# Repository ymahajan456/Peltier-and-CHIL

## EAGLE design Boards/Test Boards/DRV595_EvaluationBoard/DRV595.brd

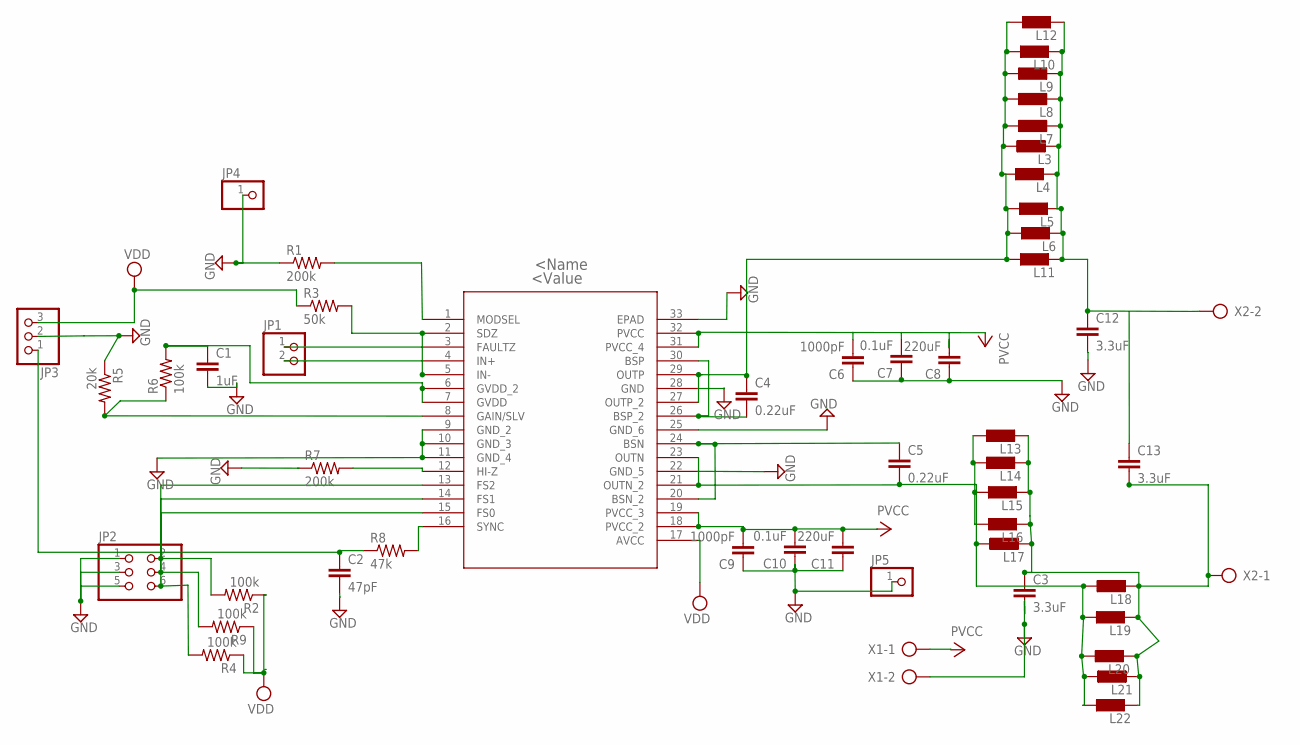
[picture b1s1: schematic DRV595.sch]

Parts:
C1: 1uF; C2.5-3
C2: 47pF; C2.5-3
C3, C12, C13: 3.3uF; C2.5-3
C4, C5: 0.22uF; C2.5-3
C6, C9: 1000pF; C2.5-3
C7, C10: 0.1uF; C2.5-3
C8, C11: 220uF; C2.5-3
JP1: PINHD-1X2; 1X02
JP2: PINHD-2X3; 2X03
JP3: PINHD-1X3; 1X03
JP4, JP5: PINHD-1X1; 1X01
L3, L4, L5, L6, L7, L8, L9, L10, L11, L12, L13, L14, L15, L16, L17, L18, L19, L20, L21, L22: L0207/10; 0207/10
R1, R7: 200k; 0207/10
R2, R4, R6, R9: 100k; 0207/10
R3: 50k; 0207/10
R5: 20k; 0207/10
R8: 47k; 0207/10
U1: DRV595DAPRDAP32_4P11X4P36-L; DAP32_4P11X4P36-L
X1: AK300/2
X2: AK500/2-H

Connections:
GND: C1.2, C2.2, C3.2, C6.1, C7.1, C8.1, C9.1, C10.1, C11.1, C12.2, JP2.1, JP2.3, JP2.5, JP3.2, JP4.1, JP5.1, R1.1, R5.1, R7.1, U1.9 (GND_2), U1.10 (GND_3), U1.11 (GND_4), U1.22 (GND_5), U1.25 (GND_6), U1.28 (GND), U1.33 (EPAD), X1.2
unnamed: R1.2, U1.1 (MODSEL)
unnamed: JP1.1, U1.4 (IN+)
unnamed: R3.2, U1.2 (SDZ), U1.3 (FAULTZ)
unnamed: R5.2, R6.1, U1.8 (GAIN/SLV)
unnamed: C1.1, R6.2, U1.6 (GVDD_2), U1.7 (GVDD)
unnamed: R7.2, U1.12 (HI-Z)
unnamed: R8.2, U1.16 (SYNC)
unnamed: C2.1, JP3.1, R8.1
unnamed: JP2.2, R2.2, U1.13 (FS2)
unnamed: C5.1, U1.20 (BSN_2), U1.24 (BSN)
unnamed: C4.2, U1.26 (BSP_2), U1.30 (BSP)
unnamed: JP2.4, R9.2, U1.14 (FS1)
unnamed: JP1.2, U1.5 (IN-)
unnamed: JP2.6, R4.2, U1.15 (FS0)
unnamed: C3.1, C13.2, L13.2, L14.2, L15.2, L16.2, L17.2, L18.2, L19.2, L20.2, L21.2, L22.2, X2.1
unnamed: C12.1, C13.1, L3.2, L4.2, L5.2, L6.2, L7.2, L8.2, L9.2, L10.2, L11.2, L12.2, X2.2
unnamed: C5.2, L13.1, L14.1, L15.1, L16.1, L17.1, L18.1, L19.1, L20.1, L21.1, L22.1, U1.21 (OUTN_2), U1.23 (OUTN)
unnamed: C4.1, L3.1, L4.1, L5.1, L6.1, L7.1, L8.1, L9.1, L10.1, L11.1, L12.1, U1.27 (OUTP_2), U1.29 (OUTP)
VCC: C6.2, C7.2, C8.2, C9.2, C10.2, C11.2, U1.18 (PVCC_2), U1.19 (PVCC_3), U1.31 (PVCC_4), U1.32 (PVCC), X1.1
VDD: JP3.3, R2.1, R3.1, R4.1, R9.1, U1.17 (AVCC)

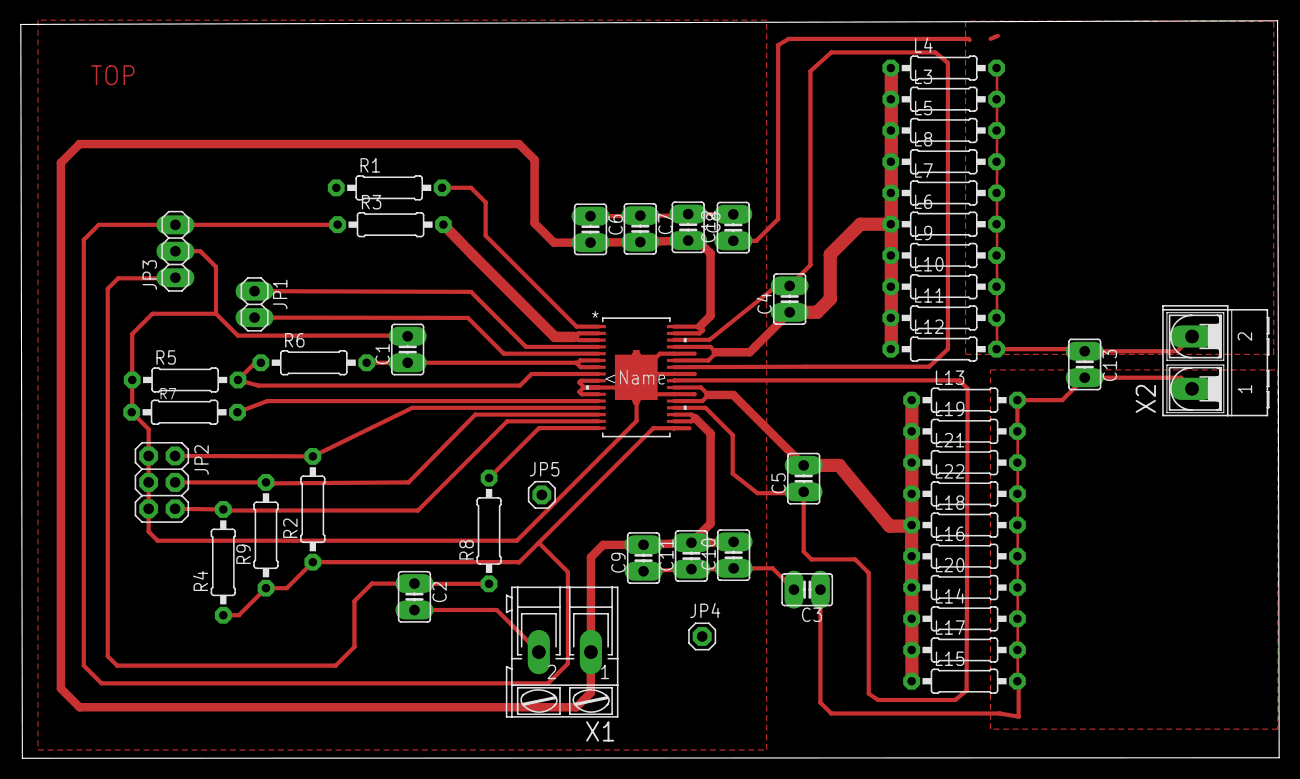
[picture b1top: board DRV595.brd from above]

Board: 2 copper layers, 120.9 x 70.8 mm, 50 parts (0 on the bottom side), 21 nets.

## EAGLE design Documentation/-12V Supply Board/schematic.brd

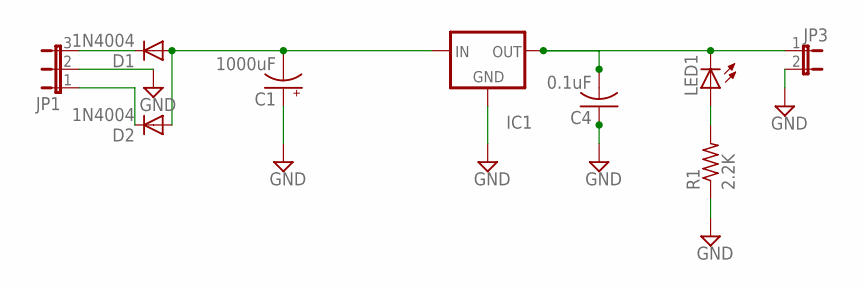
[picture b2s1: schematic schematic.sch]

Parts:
C1: 1000uF; E5-10,5
C4: 0.1uF; C050-025X075
D1, D2: 1N4004; DO41-10
IC1: 79XXS
JP1: JP2E; JP2
JP3: JP1E; JP1
LED1: LED5MM
R1: 2.2K; 0309/12

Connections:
GND: C1.+, C4.1, IC1.GND, JP1.2, JP3.2, R1.1
unnamed: D1.C, JP1.3
unnamed: D2.C, JP1.1
unnamed: C1.-, D1.A, D2.A, IC1.IN
unnamed: LED1.A, R1.2
unnamed: C4.2, IC1.OUT, JP3.1, LED1.K (C)

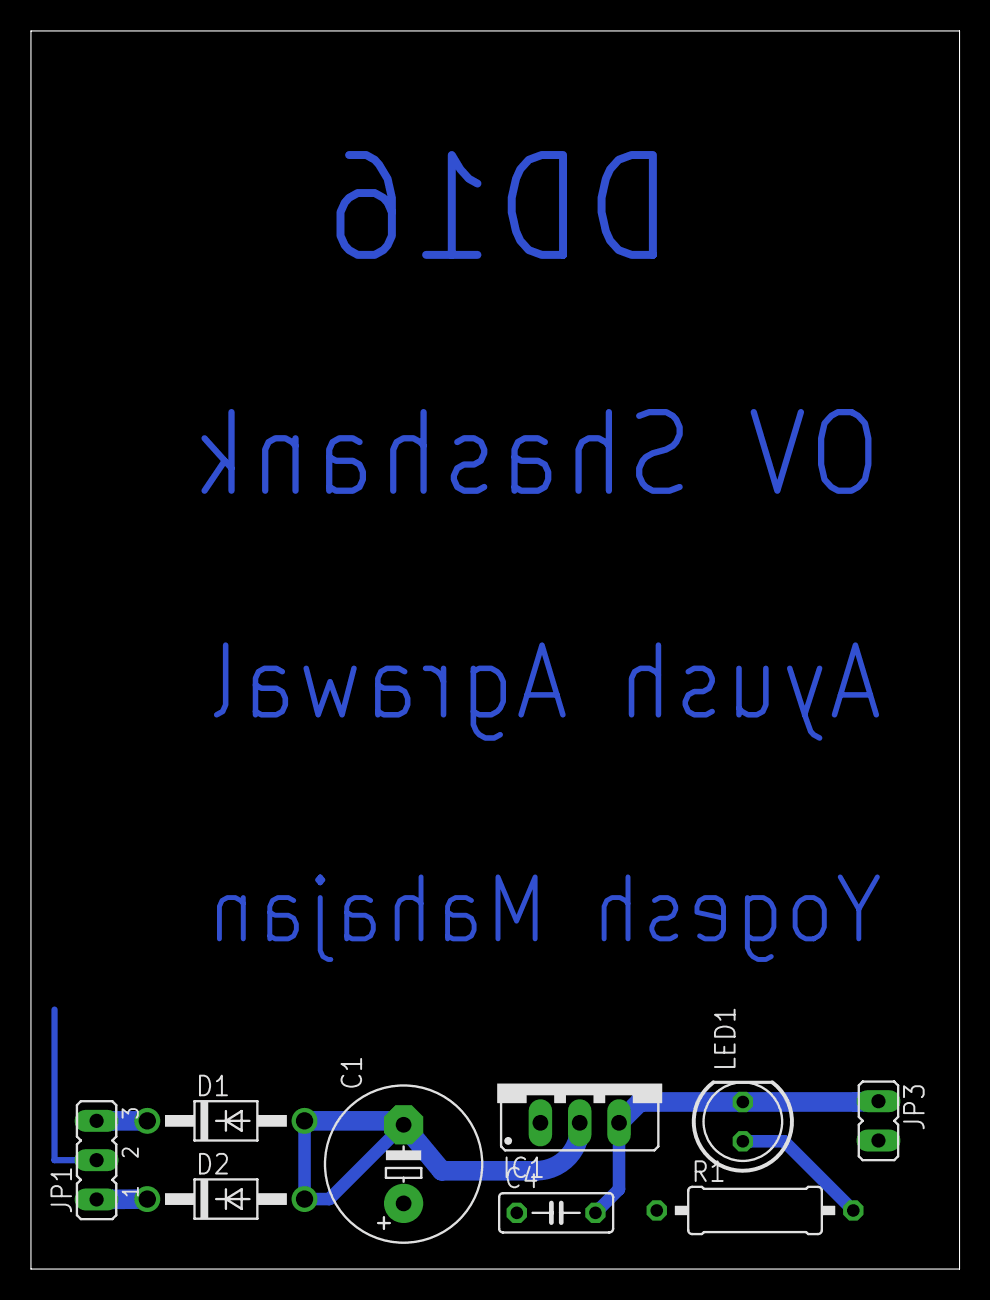
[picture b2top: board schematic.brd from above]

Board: 2 copper layers, 60.0 x 80.0 mm, 9 parts (0 on the bottom side), 6 nets.

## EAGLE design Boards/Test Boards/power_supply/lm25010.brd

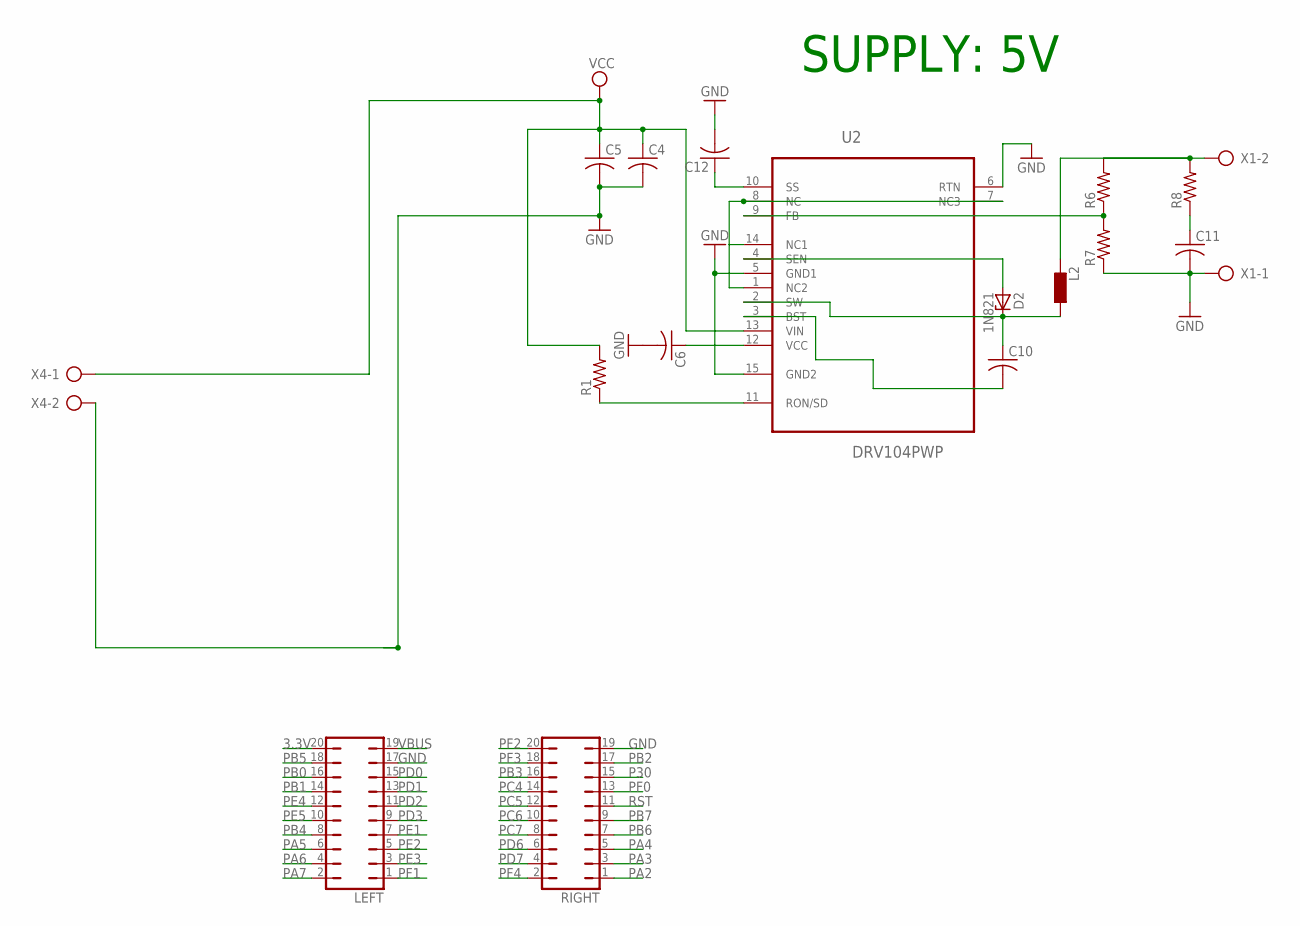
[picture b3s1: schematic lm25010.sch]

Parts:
C4, C5, C6, C10, C11, C12: C-US025-024X044; C025-024X044
D2: 1N821; DO35Z10
L2: L0207/10; 0207/10
LEFT: JP10Q
R1, R6, R7, R8: R-US_0207/10; 0207/10
RIGHT: JP10Q
U2: DRV104PWP; SOP65P640X120-15N
X1, X4: AK300/2

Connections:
3.3V: LEFT.20
GND: C4.2, C5.2, C6.2, C11.2, C12.2, LEFT.17, R7.1, RIGHT.19, U2.5 (GND1), U2.6 (RTN), U2.15 (GND2), X1.1, X4.2
unnamed: U2.1 (NC2), U2.7 (NC3), U2.8 (NC), U2.14 (NC1)
unnamed: R1.1, U2.11 (RON/SD)
unnamed: C12.1, U2.10 (SS)
unnamed: C6.1, U2.12 (VCC)
unnamed: C11.1, R8.1
unnamed: L2.2, R6.2, R8.2, X1.2
unnamed: R6.1, R7.2, U2.9 (FB)
unnamed: D2.A, U2.4 (SEN)
unnamed: C10.1, D2.C, L2.1, U2.2 (SW)
unnamed: C10.2, U2.3 (BST)
P30: RIGHT.15
PA2: RIGHT.1
PA3: RIGHT.3
PA4: RIGHT.5
PA5: LEFT.6
PA6: LEFT.4
PA7: LEFT.2
PB0: LEFT.16
PB1: LEFT.14
PB2: RIGHT.17
PB3: RIGHT.16
PB4: LEFT.8
PB5: LEFT.18
PB6: RIGHT.7
PB7: RIGHT.9
PC4: RIGHT.14
PC5: RIGHT.12
PC6: RIGHT.10
PC7: RIGHT.8
PD0: LEFT.15
PD1: LEFT.13
PD2: LEFT.11
PD3: LEFT.9
PD6: RIGHT.6
PD7: RIGHT.4
PE1: LEFT.7
PE2: LEFT.5
PE3: LEFT.3
PE4: LEFT.12
PE5: LEFT.10
PF0: RIGHT.13
PF1: LEFT.1
PF2: RIGHT.20
PF3: RIGHT.18
PF4: RIGHT.2
RST: RIGHT.11
VBUS: LEFT.19
VCC: C4.1, C5.1, R1.2, U2.13 (VIN), X4.1

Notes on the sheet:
SUPPLY: 5V

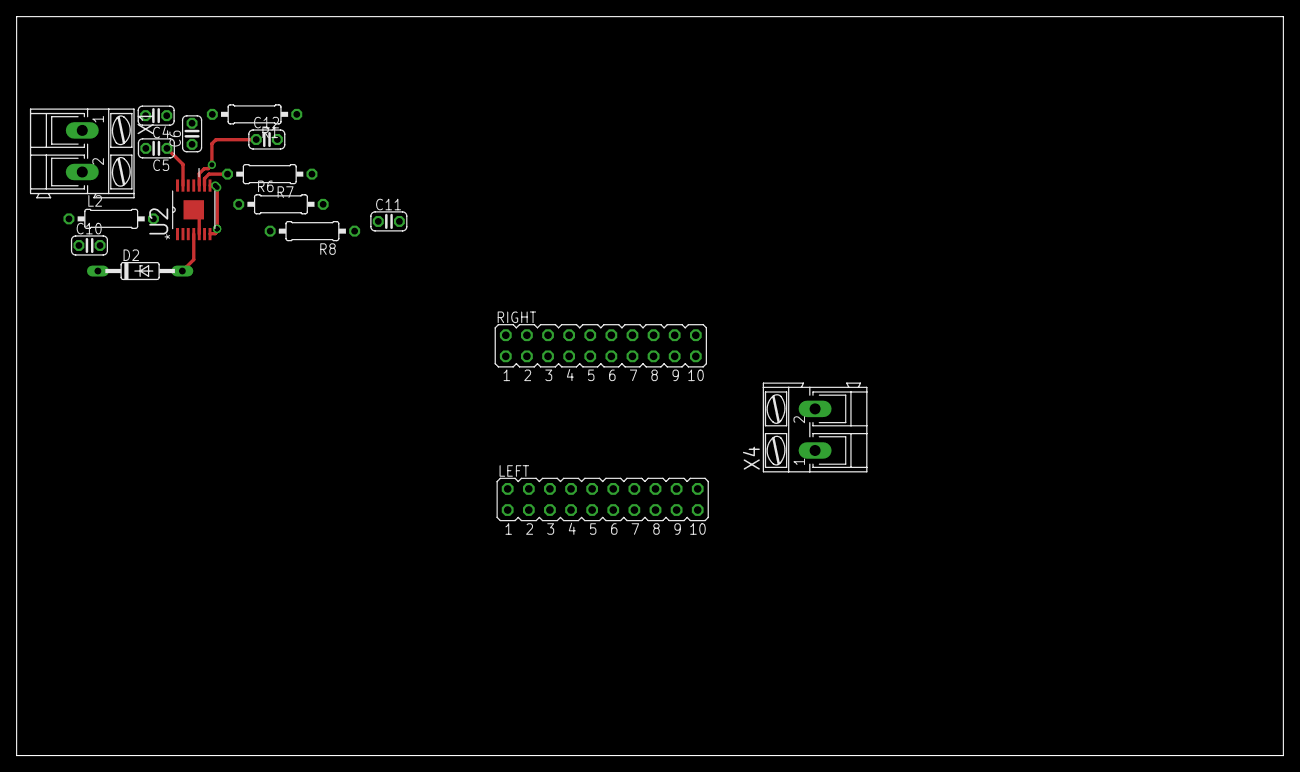
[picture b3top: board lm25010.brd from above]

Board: 2 copper layers, 152.4 x 88.9 mm, 17 parts (0 on the bottom side), 12 nets.

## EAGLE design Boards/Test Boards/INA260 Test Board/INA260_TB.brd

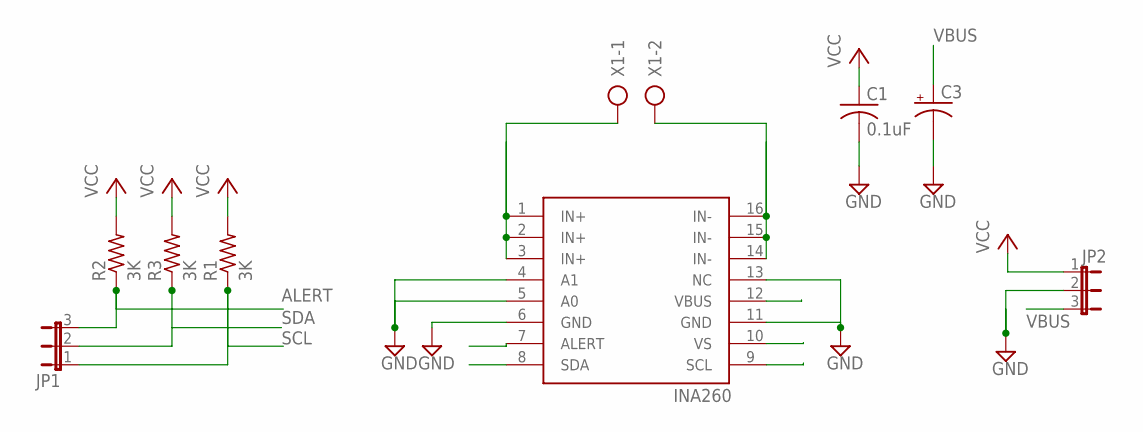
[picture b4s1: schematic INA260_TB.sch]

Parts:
C1: 0.1uF; C050-025X075
C3: CPOL-USE5-10.5; E5-10,5
JP1, JP2: JP2E; JP2
R1, R2, R3: 3K; 0207/10
U$1: INA260; TSSOP16
X1: AK300/2

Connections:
ALERT: JP1.3, R2.1, U$1.7 (ALERT)
GND: C1.2, C3.-, JP2.2, U$1.4 (A1), U$1.5 (A0), U$1.6 (GND), U$1.11 (GND), U$1.13 (NC)
unnamed: U$1.1 (IN+), U$1.2 (IN+), U$1.3 (IN+), X1.1
unnamed: U$1.14 (IN-), U$1.15 (IN-), U$1.16 (IN-), X1.2
SCL: JP1.1, R1.1, U$1.9 (SCL)
SDA: JP1.2, R3.1, U$1.8 (SDA)
VBUS: C3.+, JP2.3, U$1.12 (VBUS)
VCC: C1.1, JP2.1, R1.2, R2.2, R3.2, U$1.10 (VS)

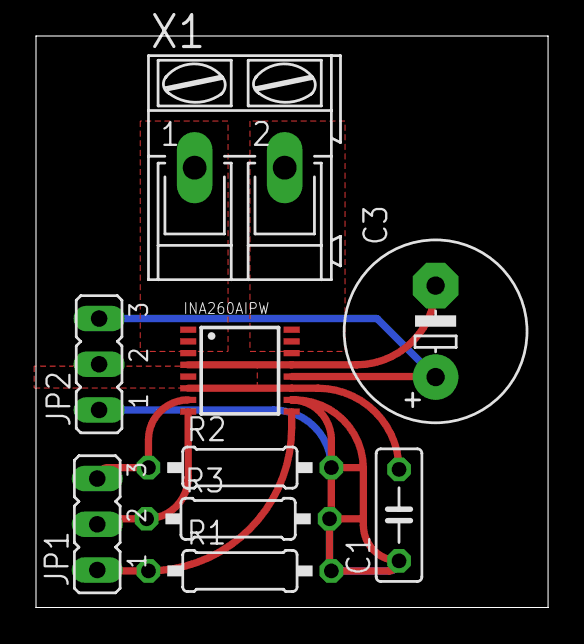
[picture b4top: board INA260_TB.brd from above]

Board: 2 copper layers, 28.4 x 31.8 mm, 9 parts (0 on the bottom side), 8 nets.

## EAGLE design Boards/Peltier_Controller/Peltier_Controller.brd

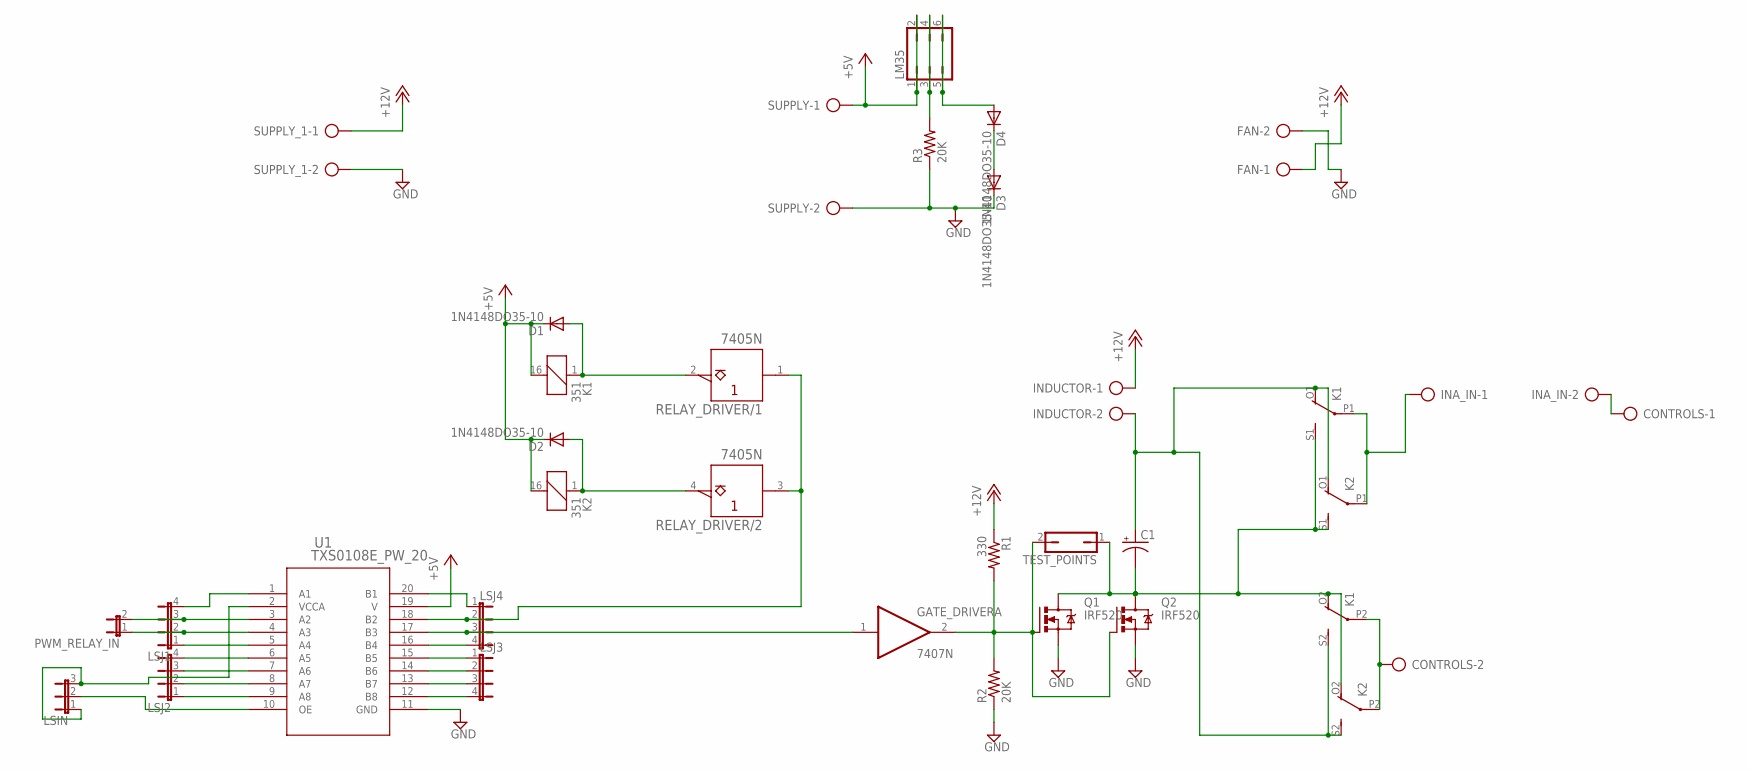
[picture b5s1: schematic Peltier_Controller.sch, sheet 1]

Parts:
C1: CPOL-USTT6D6; TT5D6
CONTROLS: AK500/2-H
D1, D2, D3, D4: 1N4148DO35-10; DO35-10
FAN: AK500/2-H
GATE_DRIVER: 7407N; DIL14
INA_IN: AK500/2-H
INDUCTOR: AK500/2-H
K1, K2: 351
LM35: JP3Q
LSIN: JP2E; JP2
LSJ1, LSJ2, LSJ3, LSJ4: JP4E; JP4
PWM_RELAY_IN: JP1E; JP1
Q1, Q2: IRF520; TO220BV
R1: 330; 0207/12
R2, R3: 20K; 0207/12
RELAY_DRIVER: 7405N; DIL14
SUPPLY: AK500/2-H
SUPPLY_1: AK500/2-H
TEST_POINTS: JP1Q; JP1
U1: TXS0108E_PW_20; PW20

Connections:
+5V: D1.C, D2.C, GATE_DRIVER.14 (VCC), K1.16 (2), K2.16 (2), LM35.1, LM35.2, RELAY_DRIVER.14 (+UB), SUPPLY.1, U1.19 (V); also elsewhere on the board
+12V: FAN.1, INDUCTOR.1, R1.1, SUPPLY_1.1
GND: D3.C, FAN.2, GATE_DRIVER.7 (GND), Q1.S, Q2.S, R2.1, R3.1, RELAY_DRIVER.7 (-UB), SUPPLY.2, SUPPLY_1.2, U1.11 (GND); also elsewhere on the board
IN+: CONTROLS.1, INA_IN.2; also elsewhere on the board
IN-: INA_IN.1, K1.P1, K2.P1; also elsewhere on the board
unnamed: LSJ1.3, PWM_RELAY_IN.2, U1.3 (A2)
unnamed: D2.A, K2.1, RELAY_DRIVER.4 (Y)
unnamed: LM35.3, LM35.4, R3.2
unnamed: D1.A, K1.1, RELAY_DRIVER.2 (Y)
unnamed: GATE_DRIVER.2 (O), Q1.G, Q2.G, R1.2, R2.2, TEST_POINTS.2
unnamed: D4.A, LM35.5, LM35.6
unnamed: D3.A, D4.C
unnamed: LSJ1.4, U1.1 (A1)
unnamed: LSJ4.1, U1.20 (B1)
unnamed: CONTROLS.2, K1.P2, K2.P2
unnamed: C1.-, K1.O2 (O), K1.S1 (S), K2.O2 (O), K2.S1 (S), Q1.D, Q2.D, TEST_POINTS.1
unnamed: LSJ1.2, PWM_RELAY_IN.1, U1.4 (A3)
unnamed: LSJ1.1, U1.5 (A4)
unnamed: LSJ2.4, U1.6 (A5)
unnamed: LSJ2.3, U1.7 (A6)
unnamed: LSJ2.2, U1.8 (A7)
unnamed: LSJ2.1, U1.9 (A8)
unnamed: LSIN.2, U1.10 (OE)
unnamed: LSIN.1, LSIN.3, U1.2 (VCCA)
unnamed: LSJ4.2, RELAY_DRIVER.1 (A), RELAY_DRIVER.3 (A), U1.18 (B2)
unnamed: GATE_DRIVER.1 (I), LSJ4.3, U1.17 (B3)
unnamed: LSJ4.4, U1.16 (B4)
unnamed: LSJ3.1, U1.15 (B5)
unnamed: LSJ3.2, U1.14 (B6)
unnamed: LSJ3.3, U1.13 (B7)
unnamed: LSJ3.4, U1.12 (B8)
VBUS: C1.+, INDUCTOR.2, K1.O1 (O), K1.S2 (S), K2.O1 (O), K2.S2 (S); also elsewhere on the board

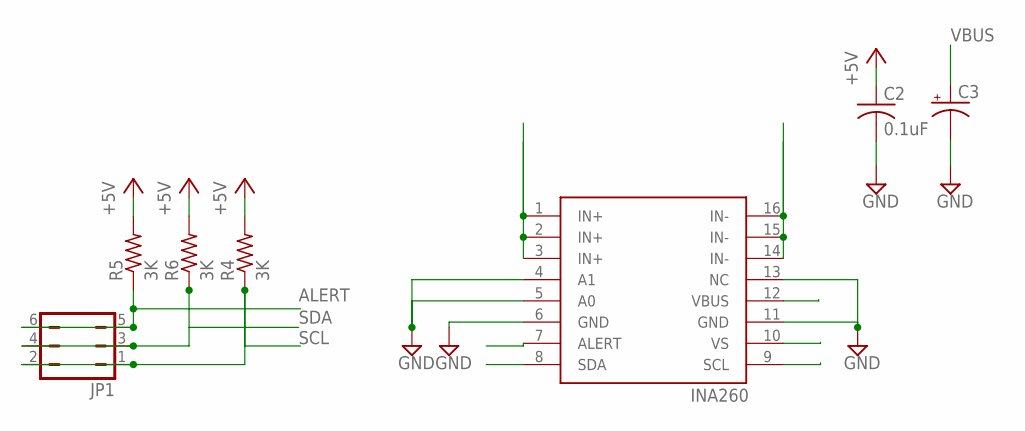
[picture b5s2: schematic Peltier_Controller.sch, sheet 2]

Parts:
C2: 0.1uF; C050-025X075
C3: CPOL-USE5-10.5; E5-10,5
JP1: JP3Q
R4, R5, R6: 3K; 0207/10
U$1: INA260; TSSOP16

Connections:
+5V: C2.1, R4.2, R5.2, R6.2, U$1.10 (VS); also elsewhere on the board
ALERT: JP1.5, JP1.6, R5.1, U$1.7 (ALERT)
GND: C2.2, C3.-, U$1.4 (A1), U$1.5 (A0), U$1.6 (GND), U$1.11 (GND), U$1.13 (NC); also elsewhere on the board
IN+: U$1.1 (IN+), U$1.2 (IN+), U$1.3 (IN+); also elsewhere on the board
IN-: U$1.14 (IN-), U$1.15 (IN-), U$1.16 (IN-); also elsewhere on the board
SCL: JP1.1, JP1.2, R4.1, U$1.9 (SCL)
SDA: JP1.3, JP1.4, R6.1, U$1.8 (SDA)
VBUS: C3.+, U$1.12 (VBUS); also elsewhere on the board

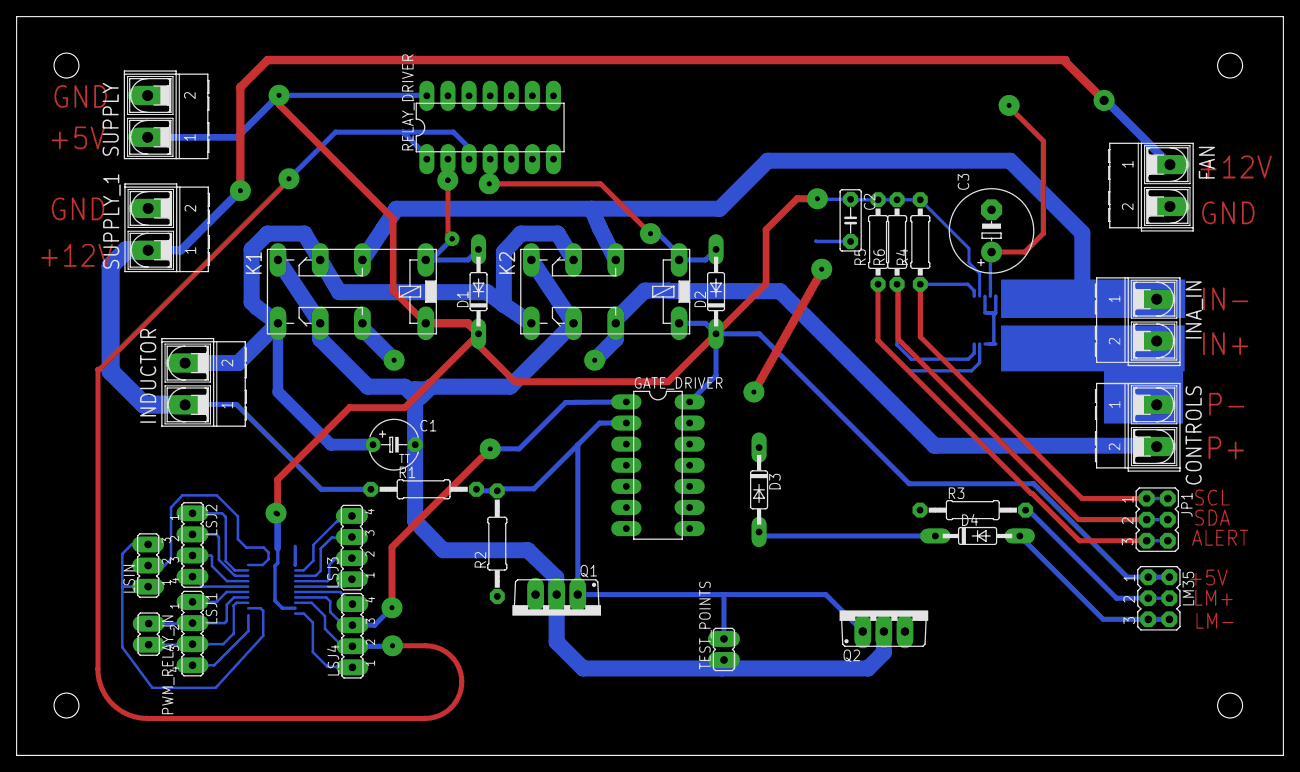
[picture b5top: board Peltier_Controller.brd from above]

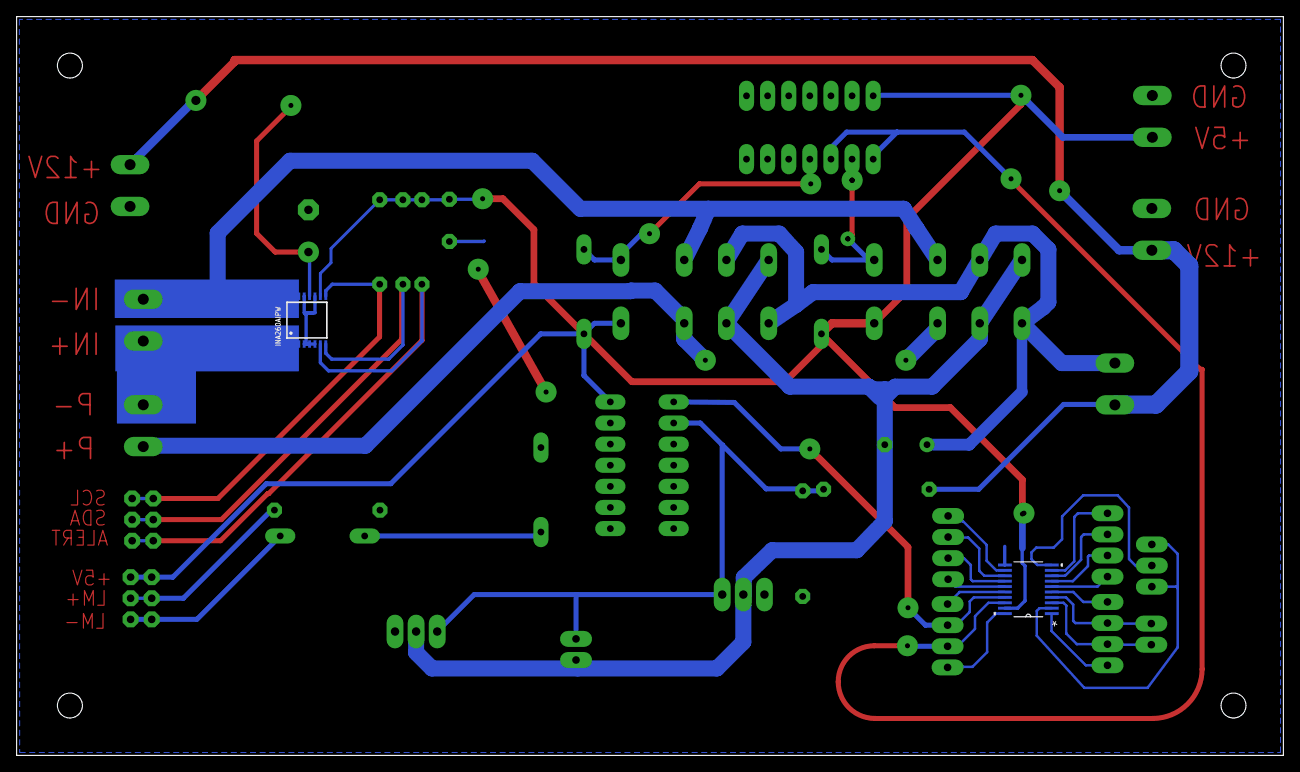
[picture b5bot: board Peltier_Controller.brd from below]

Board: 2 copper layers, 152.4 x 88.9 mm, 36 parts (2 on the bottom side), 35 nets.

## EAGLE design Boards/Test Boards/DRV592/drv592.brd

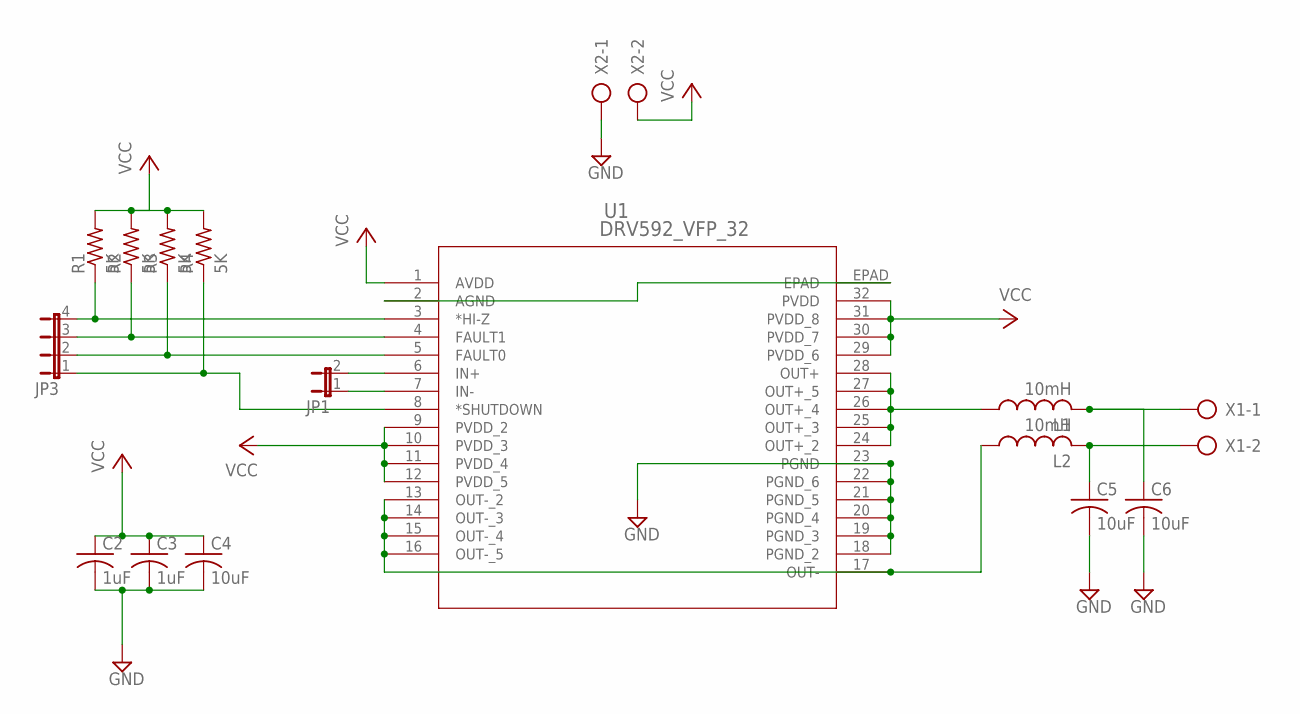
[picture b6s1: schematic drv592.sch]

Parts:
C2, C3: 1uF; C050-030X075
C4, C5, C6: 10uF; C050-030X075
JP1: JP1E; JP1
JP3: JP4E; JP4
L1, L2: 10mH; TJ3-U2
R1, R2, R3, R4: 5K; 0207/10
U1: DRV592_VFP_32; VFP32_3P91X3P91
X1, X2: AK300/2

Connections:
GND: C2.2, C3.2, C4.2, C5.2, C6.2, U1.18 (PGND_2), U1.19 (PGND_3), U1.20 (PGND_4), U1.21 (PGND_5), U1.22 (PGND_6), U1.23 (PGND), X2.1
unnamed: L1.1, U1.24 (OUT+_2), U1.25 (OUT+_3), U1.26 (OUT+_4), U1.27 (OUT+_5), U1.28 (OUT+)
unnamed: C5.1, L2.2, X1.2
unnamed: L2.1, U1.13 (OUT-_2), U1.14 (OUT-_3), U1.15 (OUT-_4), U1.16 (OUT-_5), U1.17 (OUT-)
unnamed: C6.1, L1.2, X1.1
unnamed: JP1.2, U1.6 (IN+)
unnamed: JP1.1, U1.7 (IN-)
unnamed: JP3.4, R1.1, U1.3 (*HI-Z)
unnamed: JP3.3, R2.1, U1.4 (FAULT1)
unnamed: JP3.2, R3.1, U1.5 (FAULT0)
unnamed: JP3.1, R4.1, U1.8 (*SHUTDOWN)
unnamed: U1.2 (AGND), U1.EPAD
VCC: C2.1, C3.1, C4.1, R1.2, R2.2, R3.2, R4.2, U1.1 (AVDD), U1.9 (PVDD_2), U1.10 (PVDD_3), U1.11 (PVDD_4), U1.12 (PVDD_5), U1.29 (PVDD_6), U1.30 (PVDD_7), U1.31 (PVDD_8), U1.32 (PVDD), X2.2

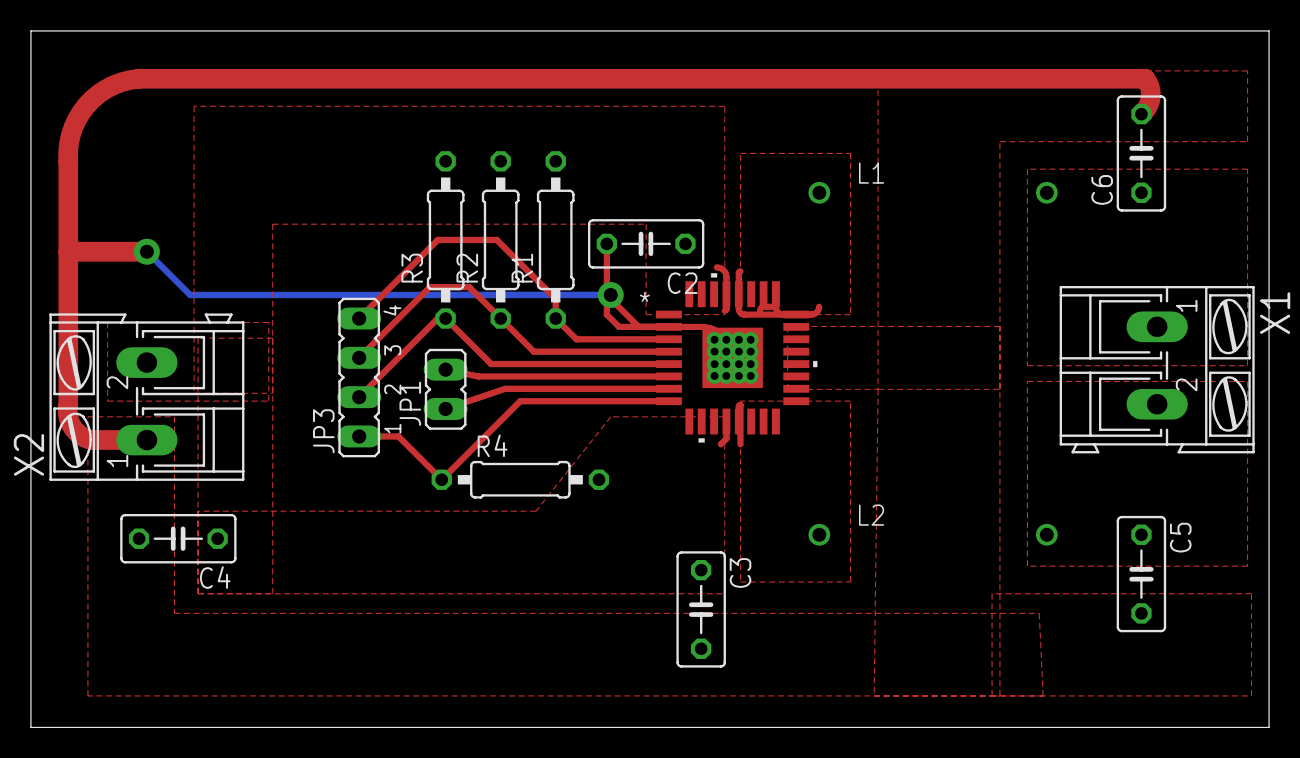
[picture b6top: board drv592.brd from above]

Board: 2 copper layers, 80.0 x 45.0 mm, 16 parts (0 on the bottom side), 13 nets.

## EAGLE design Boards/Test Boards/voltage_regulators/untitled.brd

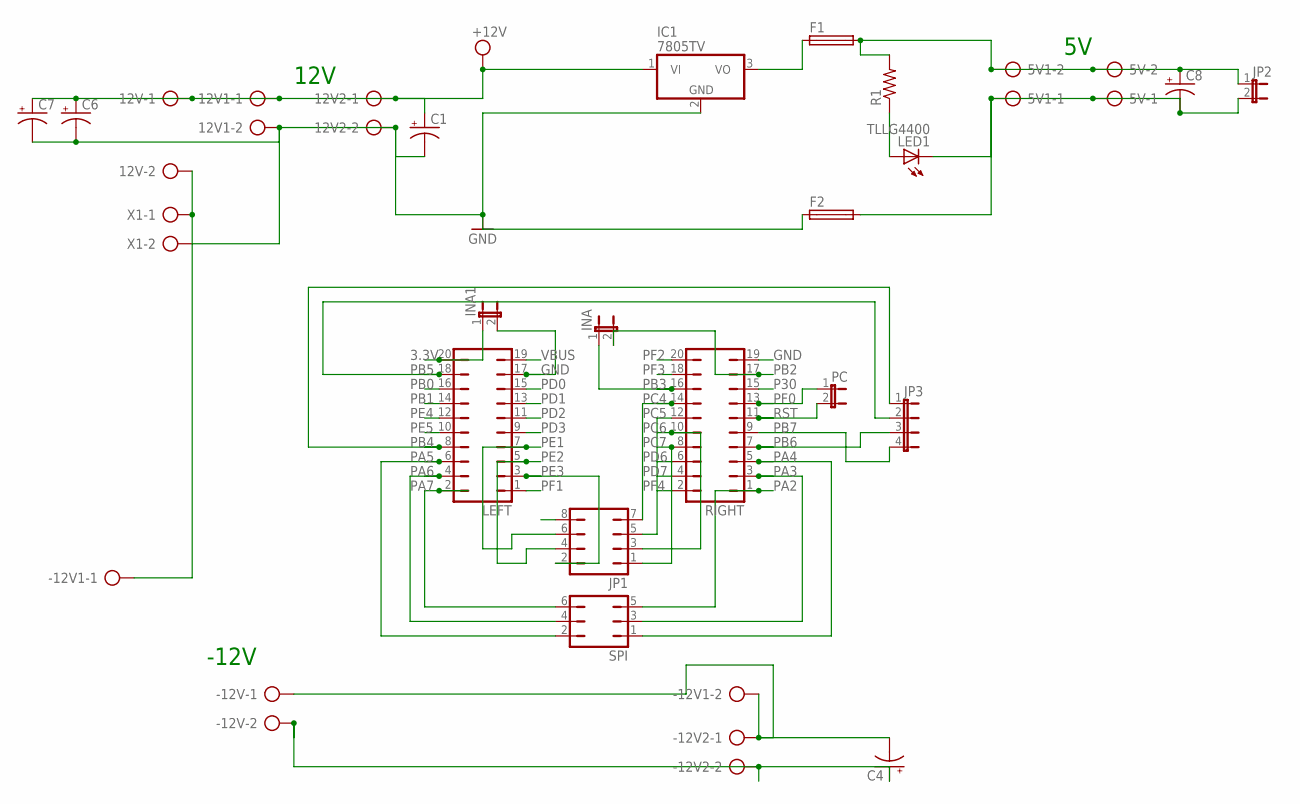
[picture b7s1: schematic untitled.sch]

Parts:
5V, 5V1, 12V, 12V1, 12V2: AK300/2
-12V, -12V1, -12V2: AK300/2
C1, C4, C6, C7, C8: CPOL-USE3.5-10; E3,5-10
F1, F2: GSH15
IC1: 7805TV; TO220V
INA, INA1: JP1E; JP1
JP1: JP4Q
JP2: JP1E; JP1
JP3: JP4E; JP4
LED1: TLLG4400; LED3MM
LEFT: JP10Q
PC: JP1E; JP1
R1: R-US_0207/10; 0207/10
RIGHT: JP10Q
SPI: JP3Q
X1: AK300/2

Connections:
3.3V: INA1.1, LEFT.20
GND: 12V1.2, 12V2.2, -12V.2, -12V2.2, C1.-, C4.+, C6.-, C7.-, F2.1, IC1.2 (GND), INA1.2, JP1.8, LEFT.17, RIGHT.19, X1.2
unnamed: F1.1, IC1.3 (VO)
unnamed: 5V.2, 5V1.2, C8.+, F1.2, JP2.1, R1.2
unnamed: 5V.1, 5V1.1, C8.-, F2.2, JP2.2, LED1.K (C)
unnamed: LED1.A, R1.1
unnamed: 12V.2, -12V1.1, X1.1
unnamed: -12V.1, -12V1.2, -12V2.1, C4.-
P30: RIGHT.15
PA2: RIGHT.1, SPI.5
PA3: RIGHT.3, SPI.3
PA4: RIGHT.5, SPI.1
PA5: LEFT.6, SPI.2
PA6: LEFT.4, SPI.4
PA7: LEFT.2, SPI.6
PB0: LEFT.16
PB1: LEFT.14
PB2: INA.2, RIGHT.17
PB3: INA.1, RIGHT.16
PB4: JP3.1, LEFT.8
PB5: JP3.2, LEFT.18
PB6: JP3.3, RIGHT.7
PB7: JP3.4, RIGHT.9
PC4: JP1.7, RIGHT.14
PC5: JP1.5, RIGHT.12
PC6: JP1.3, RIGHT.10
PC7: JP1.1, RIGHT.8
PD0: LEFT.15
PD1: LEFT.13
PD2: LEFT.11
PD3: LEFT.9
PD6: RIGHT.6
PD7: RIGHT.4
PE1: JP1.6, LEFT.7
PE2: JP1.4, LEFT.5
PE3: JP1.2, LEFT.3
PE4: LEFT.12
PE5: LEFT.10
PF0: PC.1, RIGHT.13
PF1: LEFT.1
PF2: RIGHT.20
PF3: RIGHT.18
PF4: RIGHT.2
RST: PC.2, RIGHT.11
VBUS: LEFT.19
VDD: 12V.1, 12V1.1, 12V2.1, C1.+, C6.+, C7.+, IC1.1 (VI)

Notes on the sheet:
12V
-12V

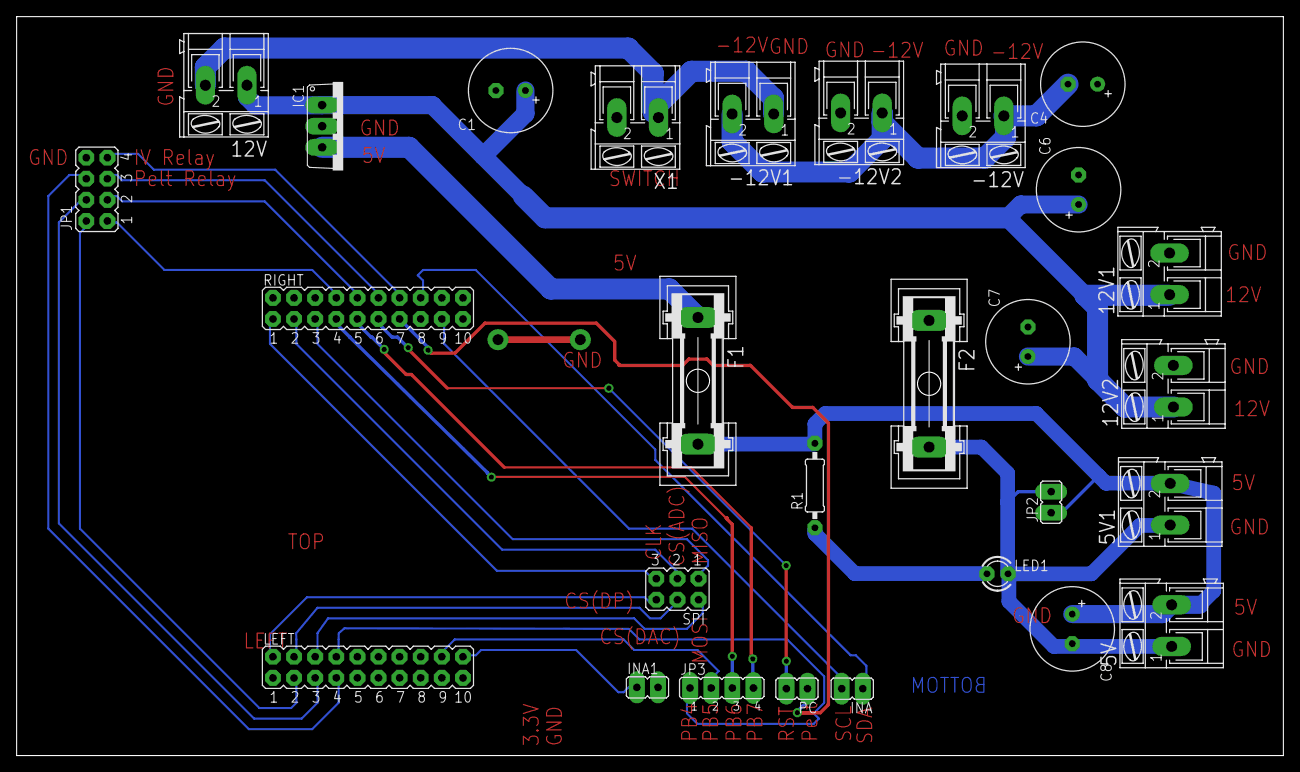
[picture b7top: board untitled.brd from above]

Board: 2 copper layers, 152.4 x 88.9 mm, 28 parts (0 on the bottom side), 30 nets.

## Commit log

2018-08-11 GitRepo Created

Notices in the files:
parts and their libraries:
COPYRIGHT: Copyright C 2016 Accelerated Designs. All rights reserved
